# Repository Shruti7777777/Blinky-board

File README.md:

✿.:* ☆:**:. Bʅιɳƙ Pυʅʂҽ .:**:.☆*.:✿

A simple LED blinking circuit designed using KiCad.

𝓟𝓻𝓸𝓳𝓮𝓬𝓽 𝓞𝓿𝓮𝓻𝓿𝓲𝓮𝔀

This project contains the schematic and PCB design for a Blinky Board. The circuit is designed to make an LED blink using the required electronic components.

𝓕𝓮𝓪𝓽𝓾𝓻𝓮𝓼

✦Designed using KiCad
✦LED blinking circuit
✦PCB heart shape layout included
✦Bill of Materials (BOM) included
✦Files Included

## Components

╰┈➤ x13 Red LEDs  
╰┈➤ x1 555 Timer IC  
╰┈➤ x1 10 µF Capacitor  
╰┈➤ x1 100k Variable Resistor  
╰┈➤ x1 10k Resistor  
╰┈➤ x1 330 Ω Resistor  
╰┈➤ x1 Push Button  
╰┈➤ x1 9V Battery Holder Clip

## Bill of Materials (BOM)

| Component | Qty | Value | Link |
|---|---:|---|---|
| Red LEDs | 13 | 5.0 mm | [Amazon](https://www.amazon.in/Self-White-Green-Yellow-Blue/dp/B0H55YYDLB/ref=sr_1_37?dib=eyJ2IjoiMSJ9.7NVeX0dixZ2cO7MW2oFZwBjvHwBzve1nDh9DZQJEhfdf7wvSMmxQX7gwJ07GlyFRvEgj7NonCyrxQ1j_sHc5IjwQQnj4ESkWuRUxtFUj9MST360svU3ZWMOBh20rHAXtEpOArRubmDhe70zKwzqcLUcXN5ECuwdqNHMO3eEhdS9yHtyWlEETA-yEzkvJ3Kh8g8j5Wodu5I54HEg3yDblh8HKqcVGniHC32BU_oeqoZmplrGYHU-vCcU5xWELi7fJZTz4J1UpIJLYh22ifOsYDr7q4GHcc87JQYNbmW5Jhmw.bx_0yLArR9mWQvjRlPQ95FaA6l6IdoidUjmKXb7rWkg&dib_tag=se&keywords=5mm+led+light&qid=1788680801&sr=8-37) |
| 555 Timer | 1 | ICM7555 | [DigiKey](LINK) |
| Capacitor | 1 | 10k | [Amazon](LINK) |
| Resistor | 2 | 330 ohm | [Amazon](https://www.amazon.in/Lalitha-resistor-kit-box-value/dp/B0D9LH4RD8) |
| Button/Switch | 2 | Push Button Switch | [Amazon](LINK) |
| Battery | 1 | 9V | [Amazon](LINK) |
| Wire | 1 | 0.6 mm | [Amazon](LINK) |
| Solder | 1 | Solder Wire | [Amazon](LINK) |

𝓦𝓱𝔂 𝓘 𝓶𝓪𝓭𝓮 𝓽𝓱𝓮 𝓹𝓻𝓸𝓳𝓮𝓬𝓽

Blink Pulse is a simple blinky board project created as part of a Hack Club hardware learning workshop. Through this project, I learned about basic electronic components, PCB design, and how a simple blinking circuit works using KiCad.

𝓗𝓸𝔀 𝓘𝓽 𝓦𝓸𝓻𝓴𝓼

The Blinky Board uses a 555 timer circuit to generate repeating electrical pulses. These pulses turn the LEDs ON and OFF repeatedly, creating a blinking effect. The resistor and capacitor help control the timing of the blinking, while the battery provides power to the circuit.

𝓓𝓮𝓶𝓸 𝓿𝓲𝓭𝓮𝓸
https://lapse.hackclub.com/timelapse/9uhOgwMm9iYm

𝘈𝘶𝘵𝘩𝘰𝘳: 𝗦𝗵𝗿𝘂𝘁𝗶 𝗞𝘂𝗺𝗮𝗿𝗶

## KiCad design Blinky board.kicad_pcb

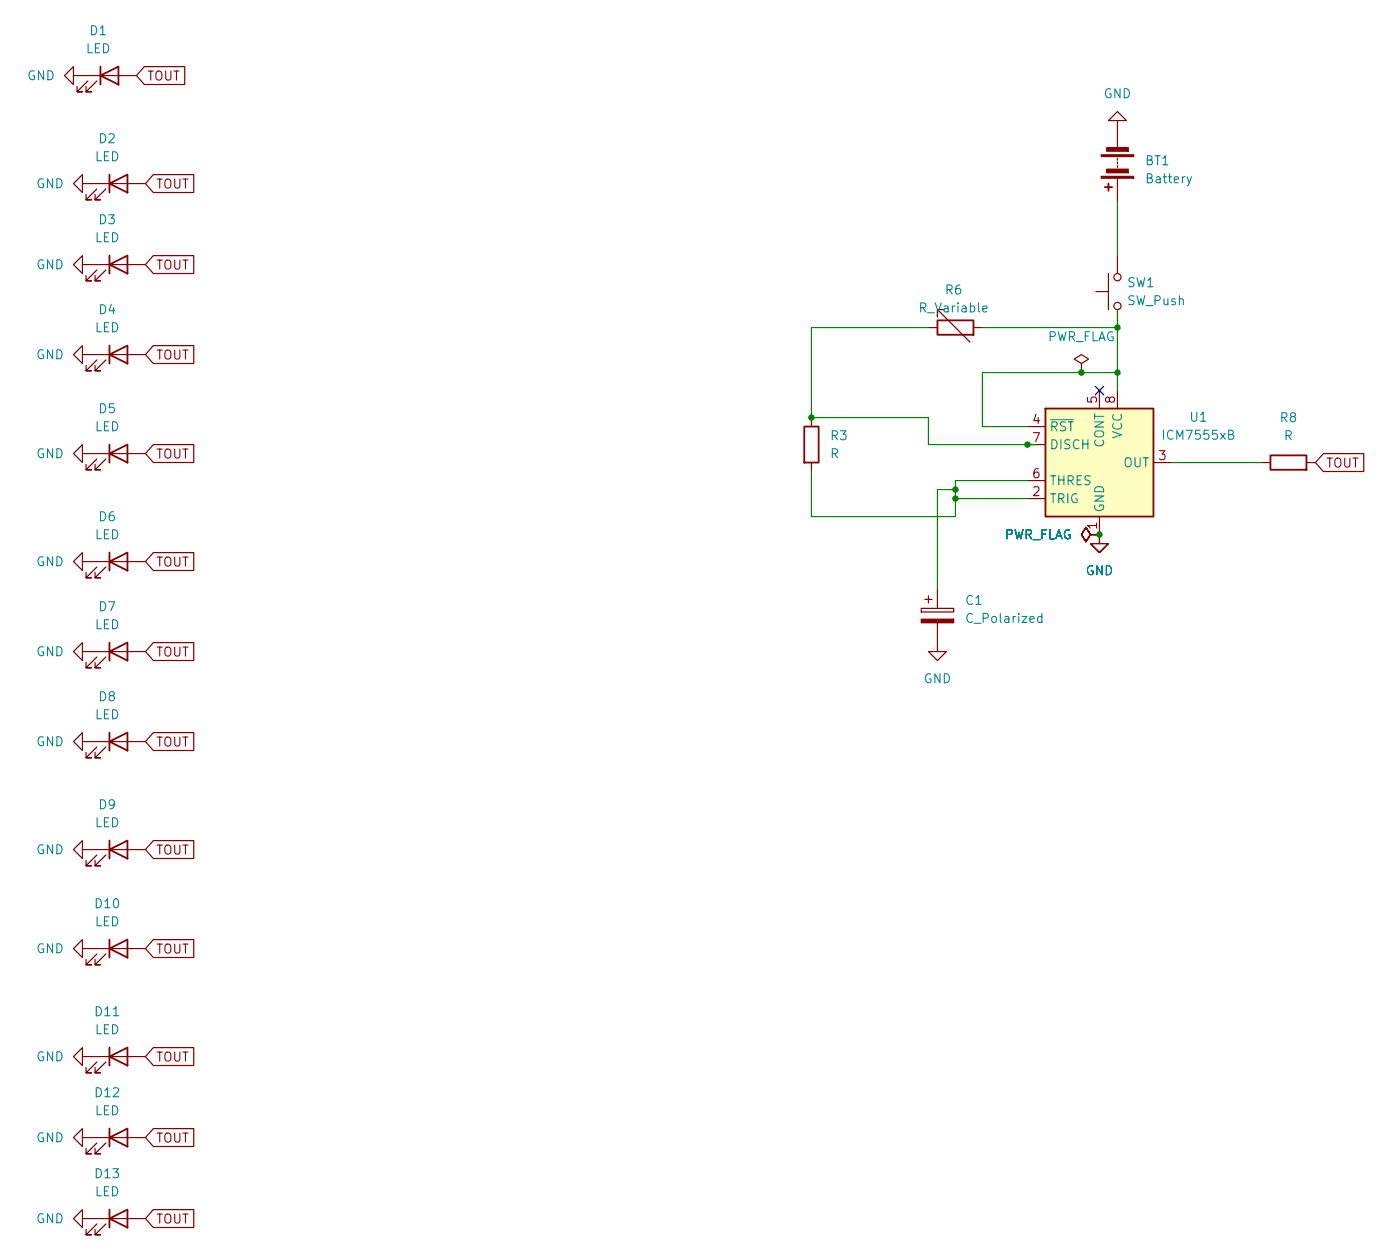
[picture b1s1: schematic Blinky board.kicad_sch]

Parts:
BT1: Battery; SolderWire-0.1sqmm_1x02_P3.6mm_D0.4mm_OD1mm
C1: C_Polarized; CP_Radial_D5.0mm_P2.50mm
D1, D2, D3, D4, D5, D6, D7, D8, D9, D10, D11, D12, D13: LED; LED_D5.0mm
R3, R8: R; R_Axial_DIN0207_L6.3mm_D2.5mm_P7.62mm_Horizontal
R6: R_Variable; Potentiometer_Bourns_3386P_Vertical
SW1: SW_Push; SW_PUSH_6mm
U1: ICM7555xB; SOIC-8_3.9x4.9mm_P1.27mm

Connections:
GND: BT1.2 (-), C1.2, D1.1 (K), D2.1 (K), D3.1 (K), D4.1 (K), D5.1 (K), D6.1 (K), D7.1 (K), D8.1 (K), D9.1 (K), D10.1 (K), D11.1 (K), D12.1 (K), D13.1 (K), U1.1 (GND)
unnamed: BT1.1 (+), SW1.2
unnamed: R3.1, R6.1, U1.7 (DISCH)
unnamed: R8.1, U1.3 (OUT)
unnamed: C1.1, R3.2, U1.2 (TRIG), U1.6 (THRES)
unnamed: R6.2, SW1.1, U1.4 (~RST), U1.8 (VCC)
TOUT: D1.2 (A), D2.2 (A), D3.2 (A), D4.2 (A), D5.2 (A), D6.2 (A), D7.2 (A), D8.2 (A), D9.2 (A), D10.2 (A), D11.2 (A), D12.2 (A), D13.2 (A), R8.2

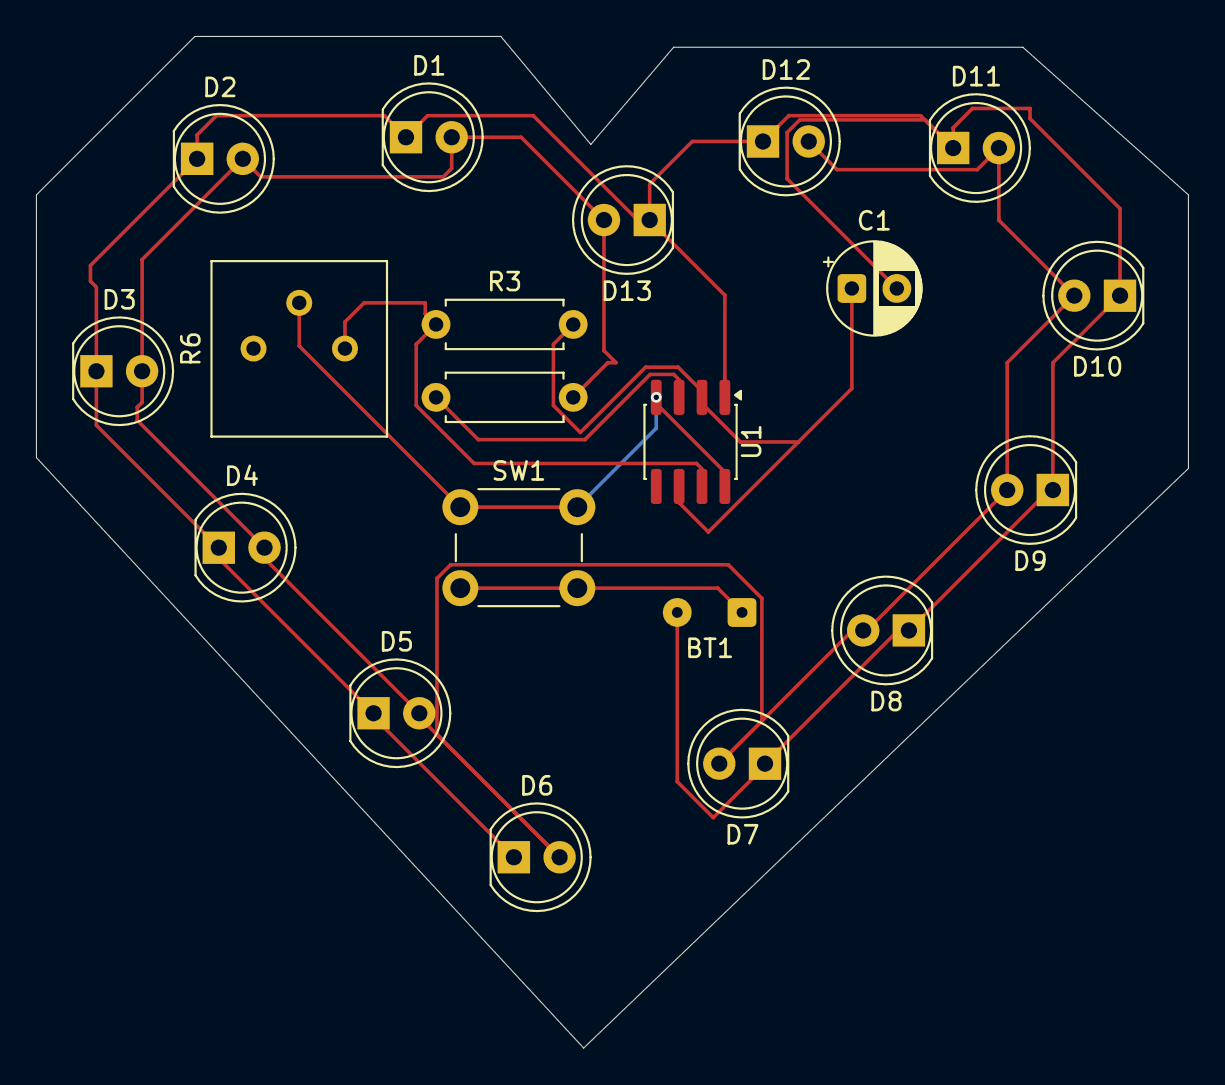
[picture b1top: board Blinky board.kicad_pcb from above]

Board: 2 copper layers, 64.0 x 56.2 mm, 20 parts (0 on the bottom side), 7 nets.

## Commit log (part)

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2026-04-18 Update README.md
    This project is held by hackathon, it'555 LED Chaser
